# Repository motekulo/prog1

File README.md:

# Prog1

A [guitar pedal](https://progpedals.com.au/pedals/) that runs patches prototyped on a Daisy Pod. 

[ProgPedals](https://progpedals.com.au) is the site dedicated to this pedal, patches, and community.

## Thanks

- For hardware thanks to work on the Dasiy Petal, the [Terrarium](https://www.pedalpcb.com/product/pcb351/), [Hothouse](https://clevelandmusicco.com/hothouse-diy-digital-signal-processing-platform-kit/) and the work of  [Keith Shepherd](https://github.com/bkshepherd)
- Timothy Schoen and other developers (Alex Mitchell, for example) for Plugdata
- Wasted Audio for the [Heavy hvcc compiler](https://wasted-audio.github.io/hvcc/)
- Graham Wakefield and Gregory Taylor for [Generating Sound and Organizing Time](https://cycling74.com/books/go)

## Videos

[ProgPedals playlist](https://www.youtube.com/playlist?list=PL_tHhignqT_7VD3HtruWB_GTngK06rujz)

## Roadmap

- Prog2 - using the [Daisy Seed2 DFM](https://electro-smith.com/pages/daisy-seed2-dfm)
- ~~ Footswitch PCBs connected via IDC cable ~~
- ~~ Better audio sockets ~~
- ~~ SMD version as well as through hole. ~~

## About me
I'm a musician/ lecturer - https://researchers.mq.edu.au/en/persons/denis-crowdy, https://codemusic.studio

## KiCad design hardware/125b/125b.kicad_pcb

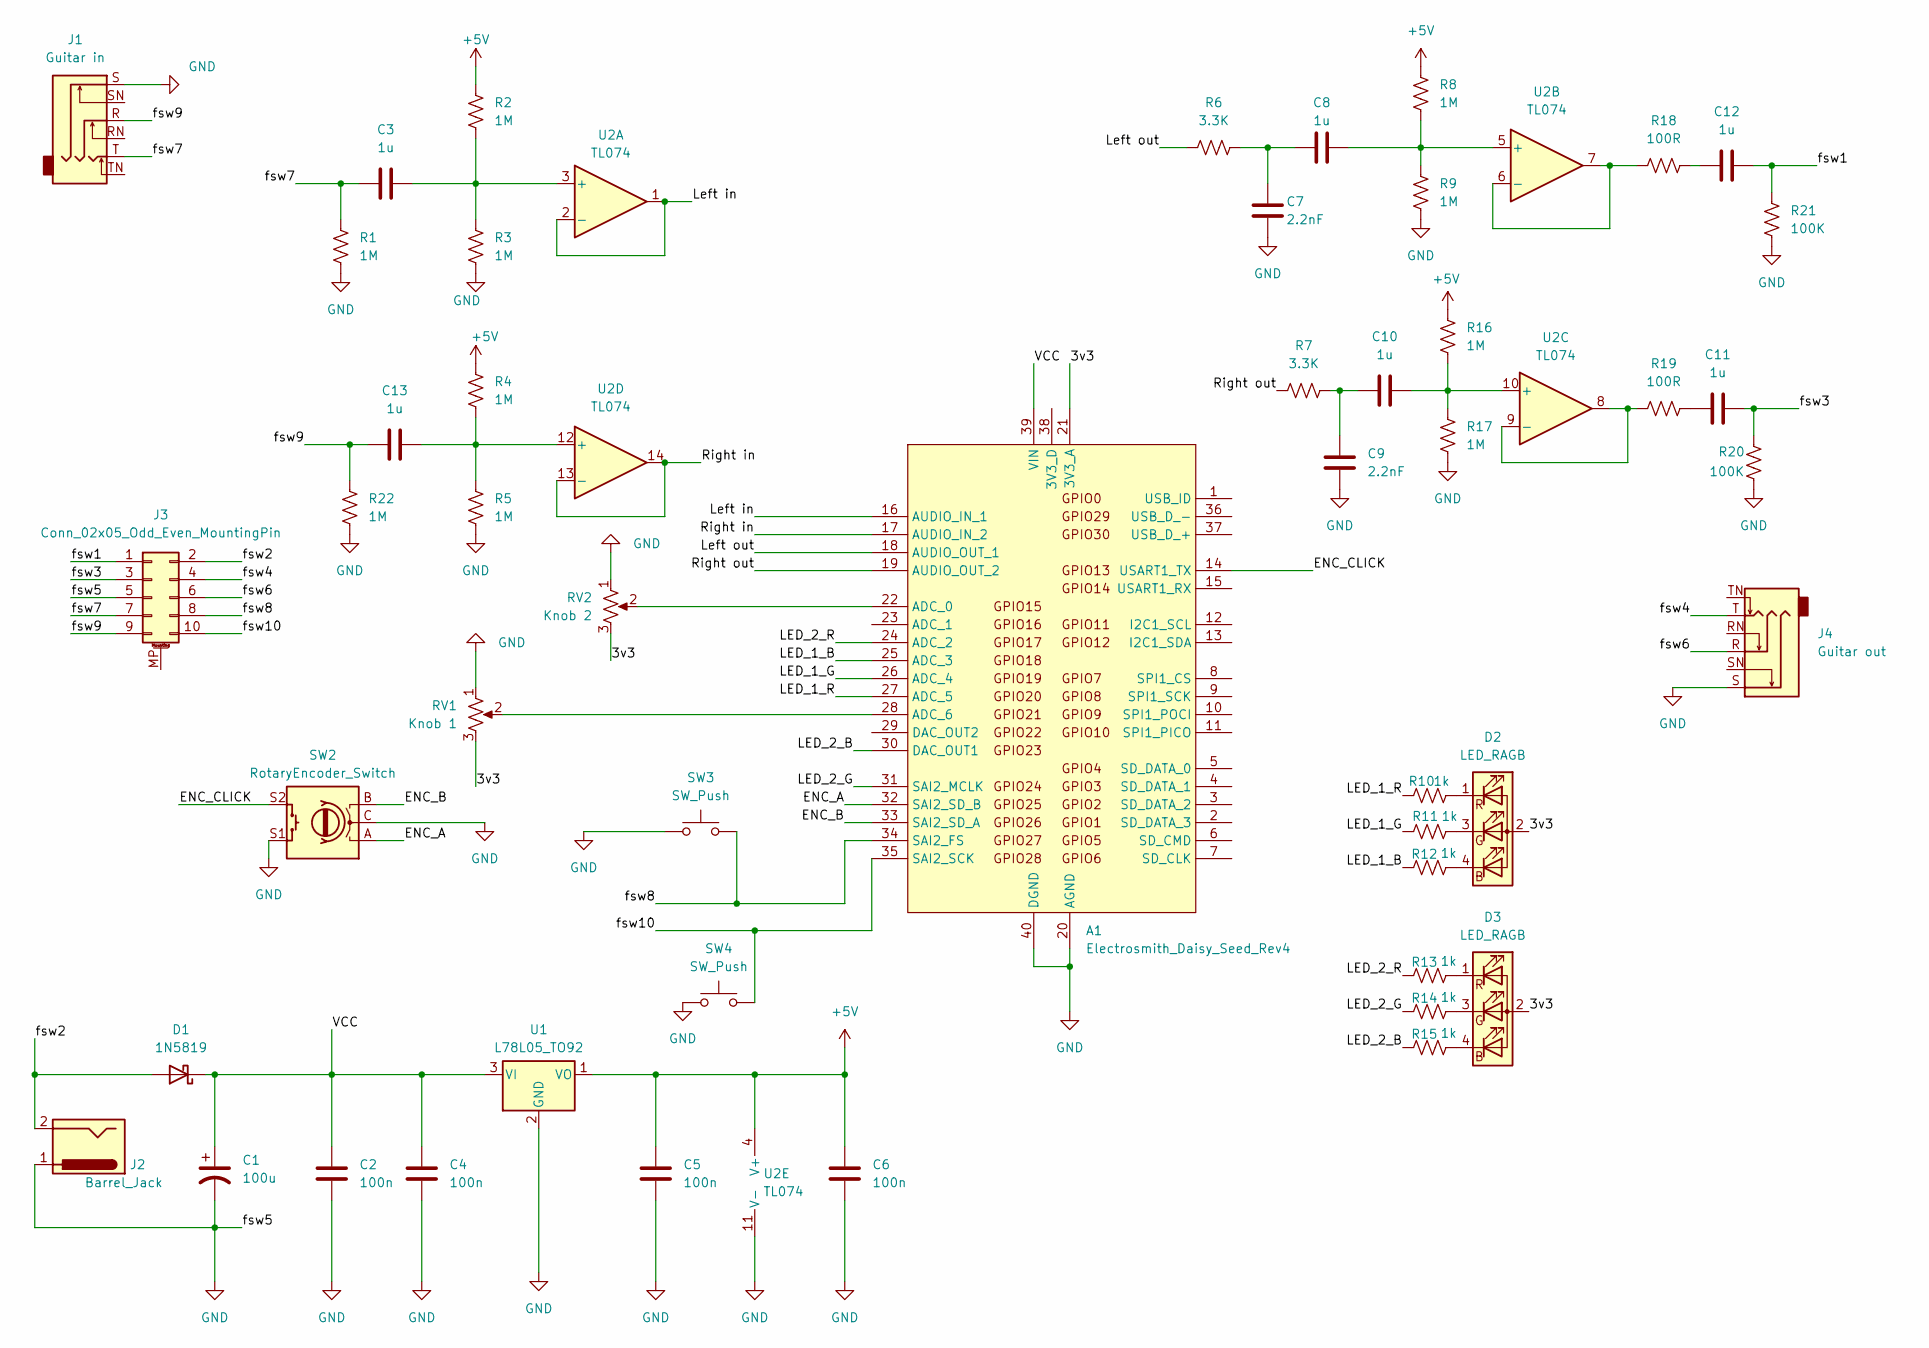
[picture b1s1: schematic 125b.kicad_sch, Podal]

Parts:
A1: Electrosmith_Daisy_Seed_Rev4; Electrosmith_Daisy_Seed
C1: 100u; C_Radial_D5.0mm_H11.0mm_P2.00mm
C2, C4, C5, C6: 100n; C_0805_2012Metric
C3, C8, C10, C11, C12, C13: 1u; C_0805_2012Metric
C7, C9: 2.2nF; C_0805_2012Metric
D1: 1N5819; D_DO-41_SOD81_P7.62mm_Horizontal
D2, D3: LED_RAGB; LED_D5.0mm-4_RGB_Wide_Pins
J1: Guitar in; Jack_6.35mm_Neutrik_NMJ6HCD2_Horizontal
J2: Barrel_Jack; BarrelJack_Horizontal
J3: Conn_02x05_Odd_Even_MountingPin; IDC-Header_2x05_P2.54mm_Vertical
J4: Guitar out; Jack_6.35mm_Neutrik_NMJ6HCD2_Horizontal
R1, R2, R3, R4, R5, R8, R9, R16, R17, R22: 1M; R_0805_2012Metric
R6, R7: 3.3K; R_0805_2012Metric
R10, R11, R12, R13, R14, R15: 1k; R_0805_2012Metric
R18, R19: 100R; R_0805_2012Metric
R20, R21: 100K; R_0805_2012Metric
RV1: Knob 1; Potentiometer_Alps_RK09K_Single_Vertical
RV2: Knob 2; Potentiometer_Alps_RK09K_Single_Vertical
SW2: RotaryEncoder_Switch; RotaryEncoder_Alps_EC12E-Switch_Vertical_H20mm
SW3, SW4: SW_Push; SolderWire-0.5sqmm_1x02_P4.6mm_D0.9mm_OD2.1mm
U1: L78L05_TO92; TO-92_Inline_Wide_78L05_dc
U2: TL074; SOIC-14_3.9x8.7mm_P1.27mm

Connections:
+5V: C5.2, C6.2, R2.1, R4.1, R8.1, R16.1, U1.1 (VO), U2.4 (V+)
/3v3: A1.21 (3V3_A), D2.2 (A), D3.2 (A), RV1.3, RV2.3
/ENC_A: A1.32 (SAI2_SD_B), SW2.A
/ENC_B: A1.33 (SAI2_SD_A), SW2.B
/ENC_CLICK: A1.14 (USART1_TX), SW2.S2
/LED_1_B: A1.25 (ADC_3), R12.1
/LED_1_G: A1.26 (ADC_4), R11.1
/LED_1_R: A1.27 (ADC_5), R10.1
/LED_2_B: A1.30 (DAC_OUT1), R15.1
/LED_2_G: A1.31 (SAI2_MCLK), R14.1
/LED_2_R: A1.24 (ADC_2), R13.1
/Left in: A1.16 (AUDIO_IN_1), U2.1, U2.2 (-)
/Left out: A1.18 (AUDIO_OUT_1), R6.1
/Right in: A1.17 (AUDIO_IN_2), U2.13 (-), U2.14
/Right out: A1.19 (AUDIO_OUT_2), R7.1
/VCC: A1.39 (VIN), C1.1, C2.2, C4.2, D1.1 (K), U1.3 (VI)
/fsw1: C12.2, J3.1, R21.1
/fsw2: D1.2 (A), J2.2, J3.2
/fsw3: C11.2, J3.3, R20.1
/fsw4: J3.4, J4.T
/fsw6: J3.6, J4.R
/fsw7: C3.1, J1.T, J3.7, R1.1
/fsw8: A1.34 (SAI2_FS), J3.8, SW3.2
/fsw9: C13.1, J1.R, J3.9, R22.1
/fsw10: A1.35 (SAI2_SCK), J3.10, SW4.2
GND: A1.20 (AGND), A1.40 (DGND), C1.2, C2.1, C4.1, C5.1, C6.1, C7.1, C9.1, J1.S, J2.1, J3.5, J4.S, R1.2, R3.2, R5.2, R9.2, R17.2, R20.2, R21.2, R22.2, RV1.1, RV2.1, SW2.C, SW2.S1, SW3.1, SW4.1, U1.2 (GND), U2.11 (V-)
unnamed: A1.22 (ADC_0), RV2.2
unnamed: A1.28 (ADC_6), RV1.2
unnamed: C7.2, C8.1, R6.2
unnamed: C9.2, C10.1, R7.2
unnamed: C11.1, R19.2
unnamed: C12.1, R18.2
unnamed: D2.4 (BK), R12.2
unnamed: D2.3 (GK), R11.2
unnamed: D2.1 (RK), R10.2
unnamed: D3.4 (BK), R15.2
unnamed: D3.3 (GK), R14.2
unnamed: D3.1 (RK), R13.2
unnamed: C3.2, R2.2, R3.1, U2.3 (+)
unnamed: C8.2, R8.2, R9.1, U2.5 (+)
unnamed: R18.1, U2.6 (-), U2.7
unnamed: C10.2, R16.2, R17.1, U2.10 (+)
unnamed: R19.1, U2.8, U2.9 (-)
unnamed: C13.2, R4.2, R5.1, U2.12 (+)

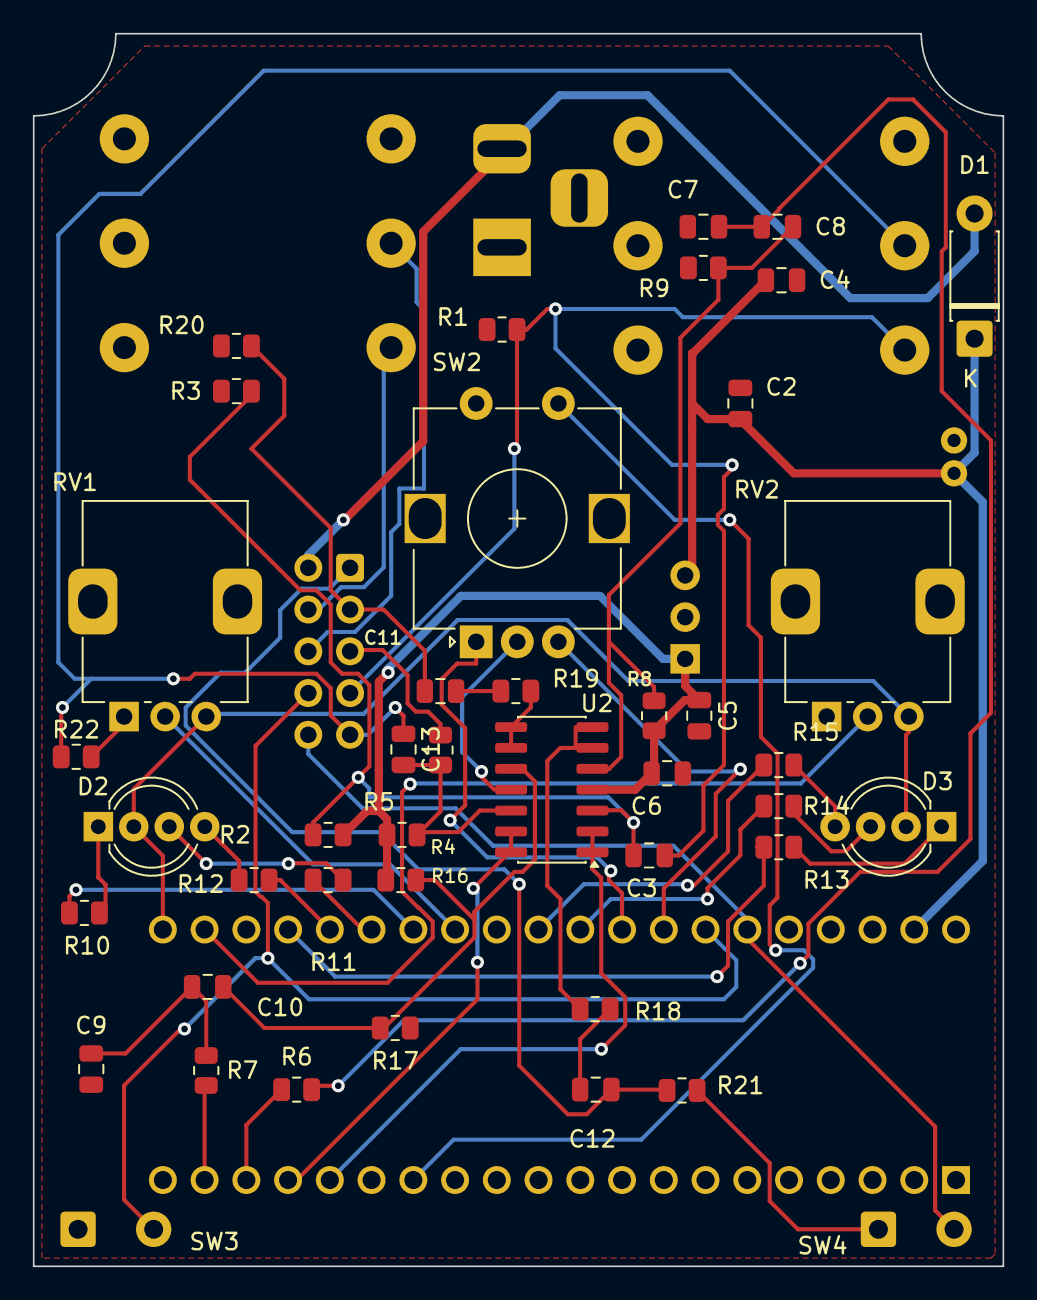
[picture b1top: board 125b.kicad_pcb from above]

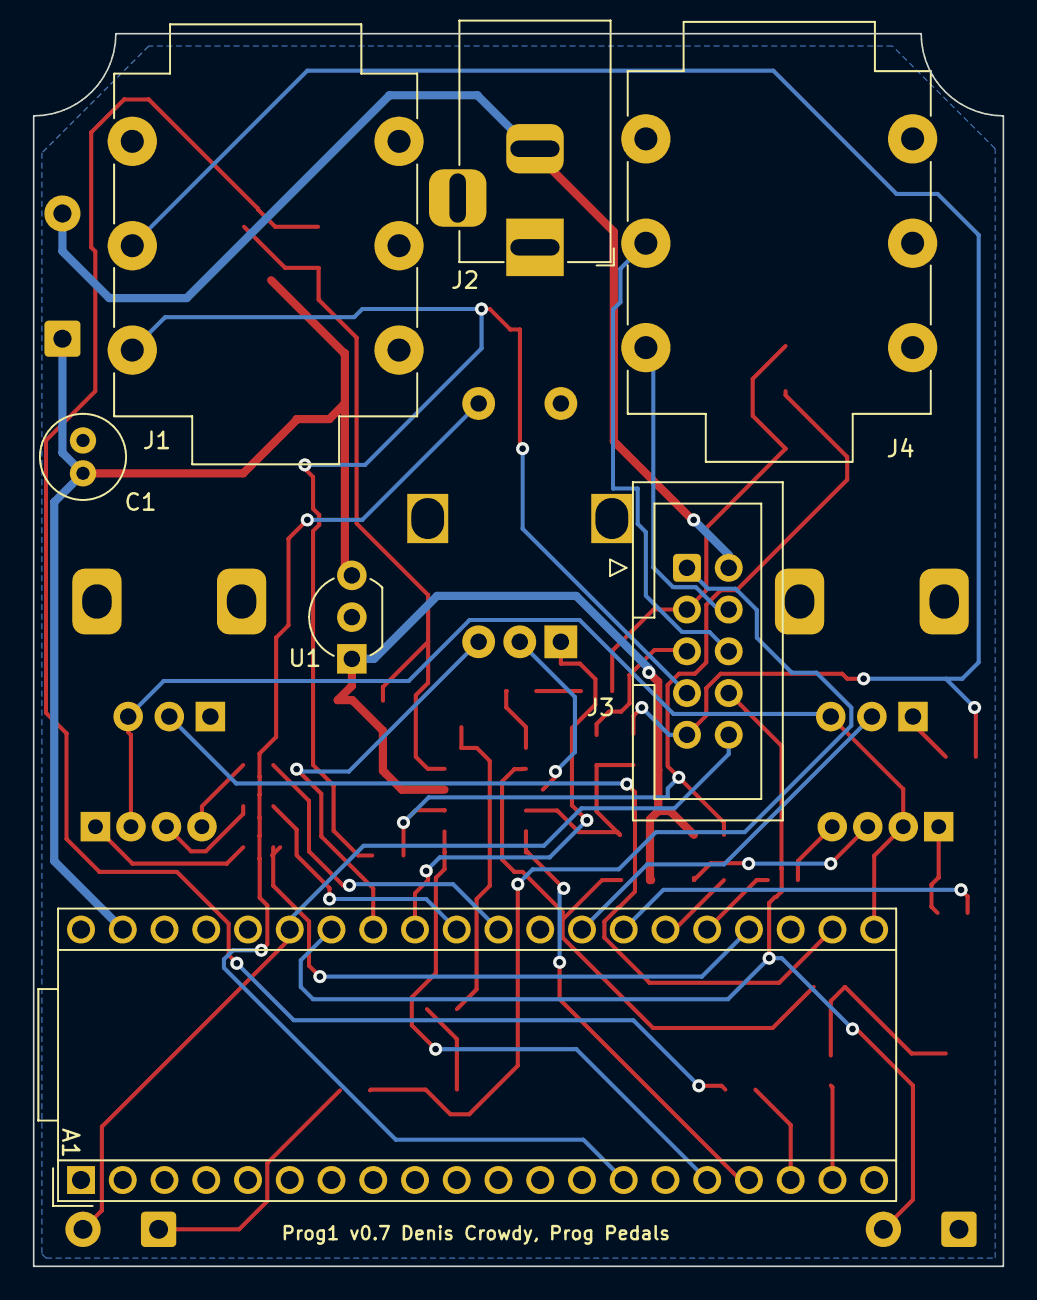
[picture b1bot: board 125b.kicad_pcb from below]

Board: 2 copper layers, 59.0 x 75.0 mm, 50 parts (7 on the bottom side), 44 nets.

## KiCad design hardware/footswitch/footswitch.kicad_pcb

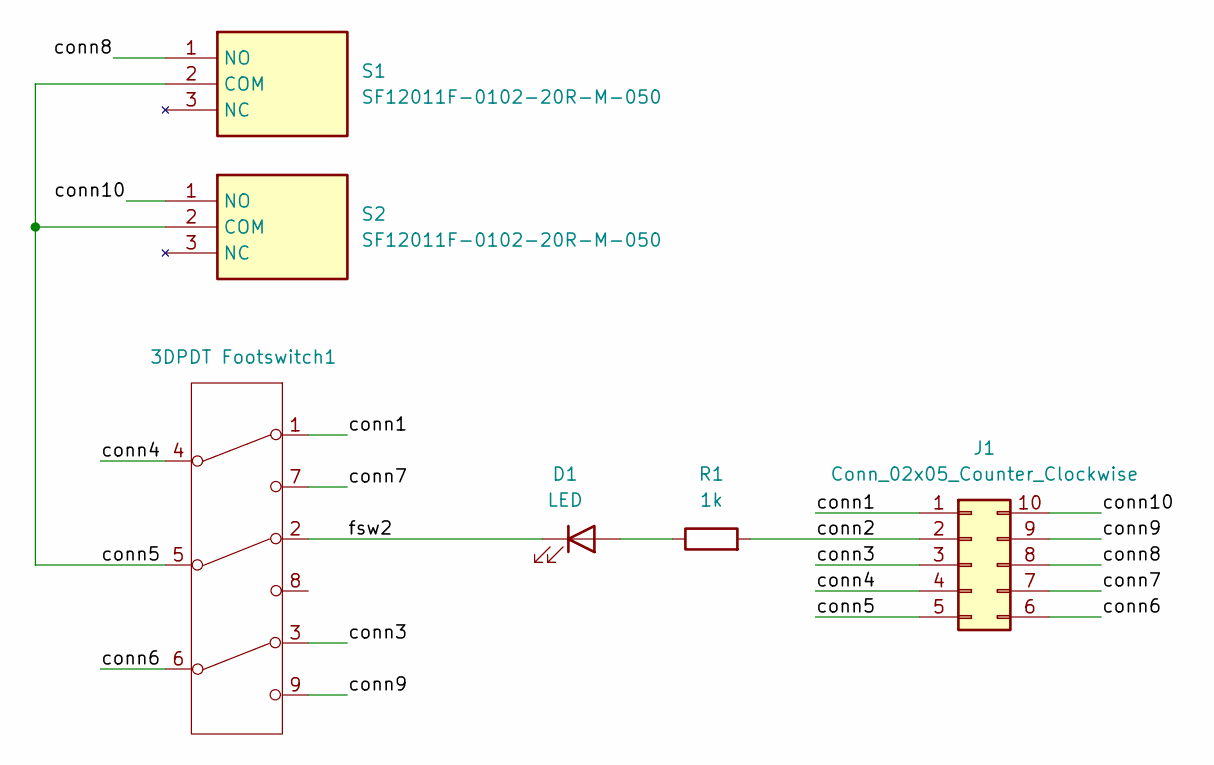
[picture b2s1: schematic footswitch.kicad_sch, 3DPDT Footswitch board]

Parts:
3DPDT Footswitch1: 0.7 footswitches - 3dpdt tayda
D1: LED; LED_D1.8mm_W3.3mm_H2.4mm
J1: Conn_02x05_Counter_Clockwise; IDC-Header_2x05_P2.54mm_Vertical
R1: 1k; R_Axial_DIN0207_L6.3mm_D2.5mm_P10.16mm_Horizontal
S1, S2: SF12011F-0102-20R-M-050; 0.7 footswitches; Mouser Part Number 107-SF12011F-102-M

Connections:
/conn1: 3DPDT Footswitch1.1 (A), J1.1
/conn2: J1.2, R1.2
/conn3: 3DPDT Footswitch1.3 (C), J1.3
/conn4: 3DPDT Footswitch1.4 (D), J1.4
/conn5: 3DPDT Footswitch1.5 (E), J1.5, S1.2 (COM), S2.2 (COM)
/conn6: 3DPDT Footswitch1.6 (F), J1.6
/conn7: 3DPDT Footswitch1.7 (G), J1.7
/conn8: J1.8, S1.1 (NO)
/conn9: 3DPDT Footswitch1.9 (G), J1.9
/conn10: J1.10, S2.1 (NO)
/fsw2: 3DPDT Footswitch1.2 (B), D1.1 (K)
unnamed: D1.2 (A), R1.1

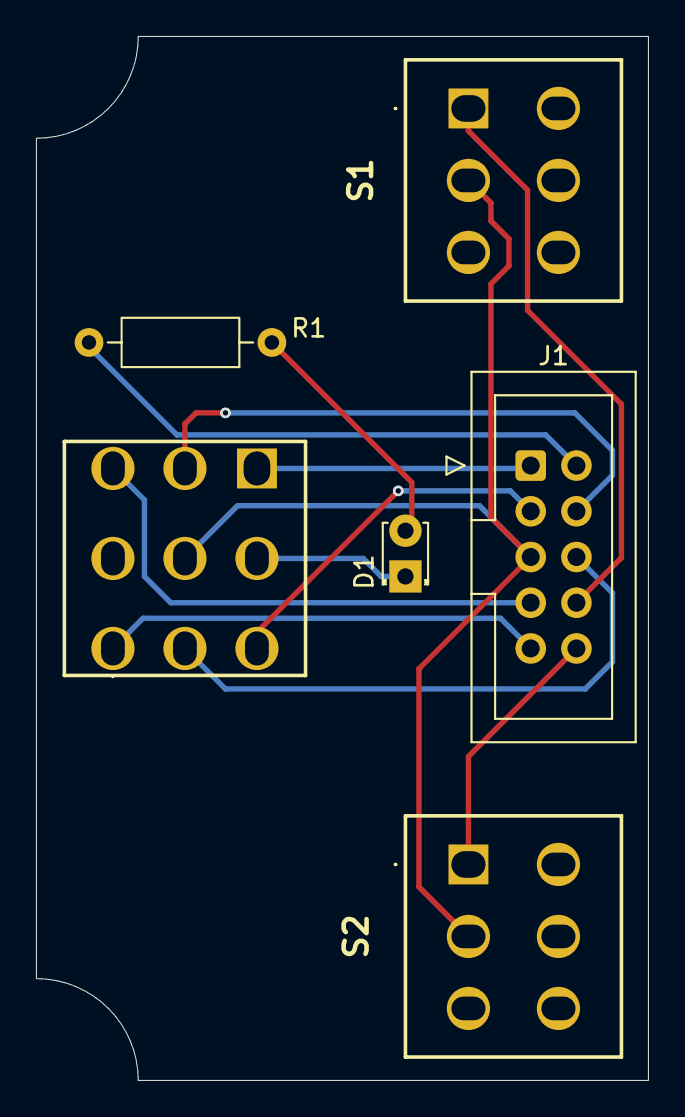
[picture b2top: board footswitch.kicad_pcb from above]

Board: 2 copper layers, 34.0 x 58.0 mm, 6 parts (0 on the bottom side), 12 nets.

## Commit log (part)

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2025-10-02 Thinner neutrik audio sockets
    ALlows power socket to move to back of board again
2025-10-02 Get everything connected
2025-10-02 Tiday up references on board and move c1
2025-10-03 Trace and component adjustments
    Also add local footprints
2025-10-03 Track adjustments to footswitch board
2025-10-04 Adjust footprint for dpdt alpha
2025-10-05 Add footprints and 3d model
2025-10-05 Name change from Crouds to Prog1 on PCB
2025-10-05 Move some labels
2025-10-07 Move resistor so switch sections could be cut off
    Might want a different switch connected directly to main pcb
2025-10-16 Add user drawings for pot and switch spindles
    Also LED on footswitch
2025-10-16 Add drill template file for 0.6
    Incomplete
2025-10-16 Align drill holes, adjust d3 y pos
    Labels on separate layer
2025-10-27 Rename project from 'Crouds' to 'Prog1'
    Updated project name and description in README.
2025-10-28 Tagging version 0.6
2025-10-29 Add reverb patch
2025-11-03 Fix line in switch footprint and update pcb
2025-11-03 Rotate the audio sockets (and correct the 3d model orientation)
2025-11-03 Update version number on board
2025-11-03 Reconnect, adjust some positions, and tweak
2025-11-03 Put D2 and D3 in same y position
2025-11-03 Bevel bottom corners of footswitch board to fit 125b corners
2025-11-03 Adjust footprints for Tayda compact footswitches
2025-11-04 Remove line in switch - TL074 is fine
2025-11-04 Minor tweaks and checks to footswitch
2025-11-05 Tidy up labels on main pcb
2025-11-20 Add chorus patch and associated binary file
2025-11-24 Fix pad nums on 3dpdt footprint and rotate on board
2026-02-12 Add Blooming Sparkles patch
2026-02-15 Add sparkles binary file
2026-02-18 Binary should have same name as patch
